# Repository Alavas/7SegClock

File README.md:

7SegClock
=========

4-Digit 7-Segment Alarm Clock

Added Lattice FGPA files.

Updated Propeller files to add MIT license.

Added new Kicad schematic.

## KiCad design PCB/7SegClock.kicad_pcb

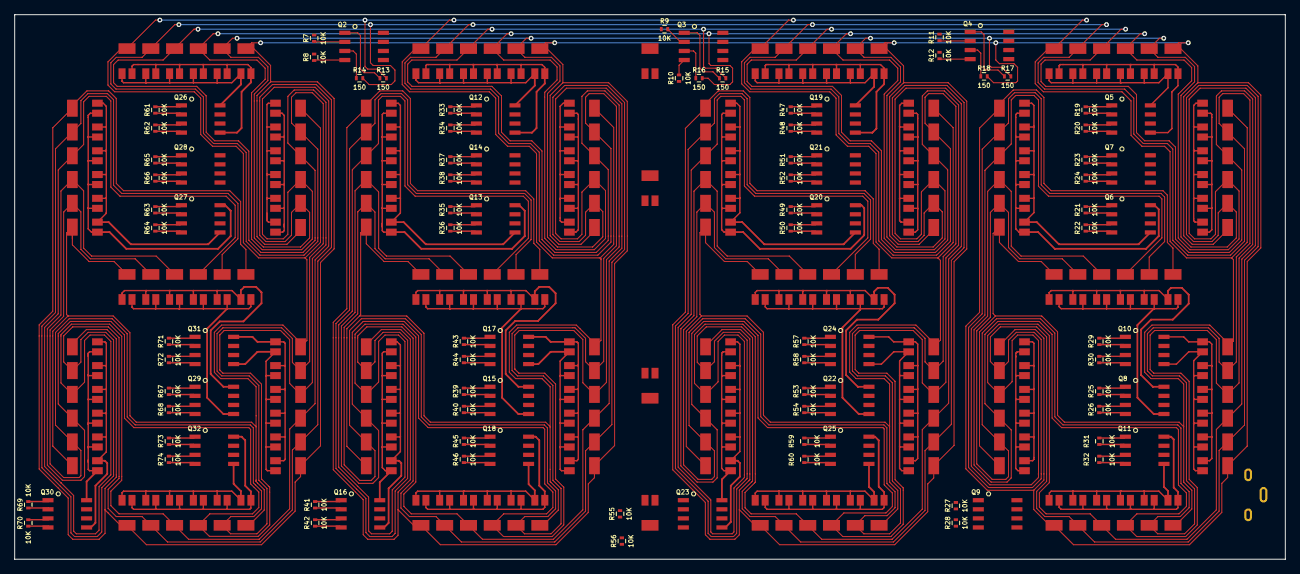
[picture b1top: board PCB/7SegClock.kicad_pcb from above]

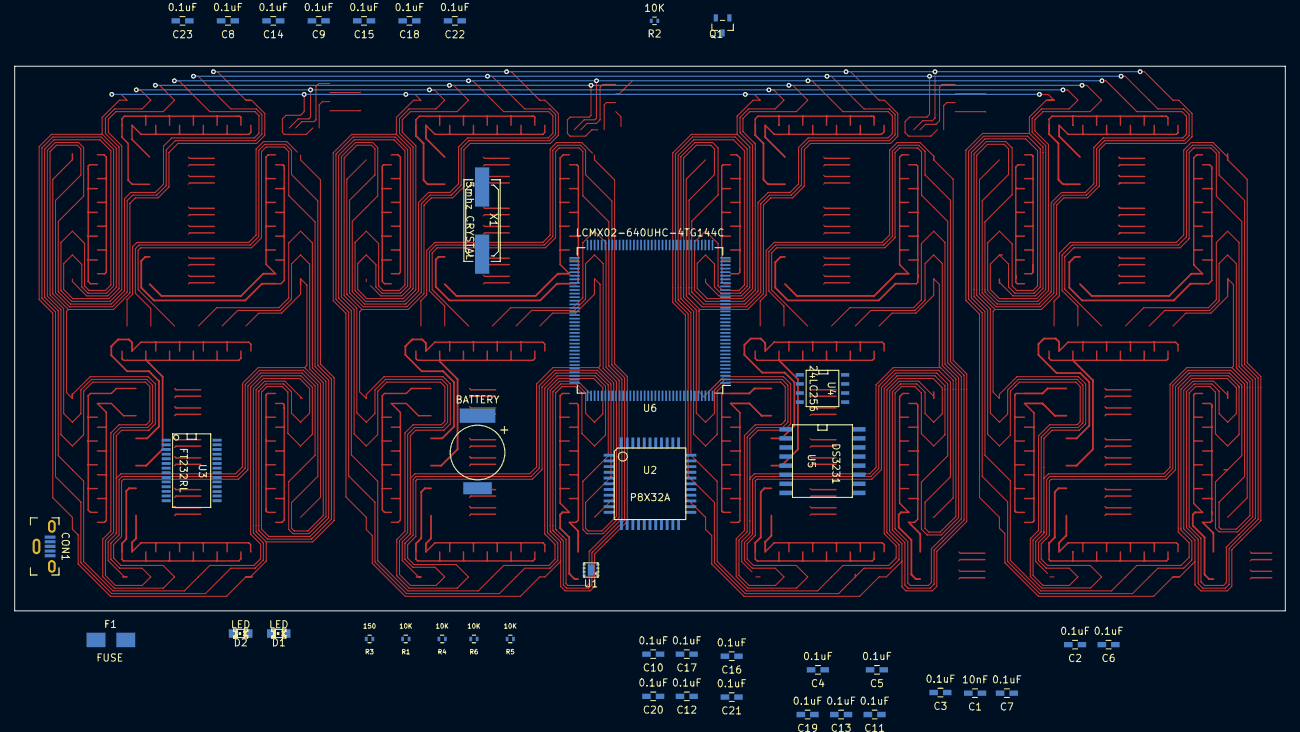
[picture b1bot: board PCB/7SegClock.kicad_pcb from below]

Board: 2 copper layers, 177.8 x 76.2 mm, 143 parts (42 on the bottom side), 158 nets.

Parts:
BT1: BATTERY; SuperCap_604-1020-1-ND
C1: 10nF; C_0603_HandSoldering
C2, C3, C4, C5, C6, C7, C8, C9, C10, C11, C12, C13, C14, C15, C16, C17, C18, C19, C20, C21, C22, C23: 0.1uF; C_0603_HandSoldering
CON1: USB_Micro_Vertical; MicroSD_Vertical
D1, D2: LED; LED-0805
D3: LED_Array; LED-ARRAY
D4: Indicators; SingleLED
F1: FUSE; Fuse_SMD1206_HandSoldering
Q1: NPN; sot23
Q2, Q3, Q4, Q5, Q6, Q7, Q8, Q9, Q10, Q11, Q12, Q13, Q14, Q15, Q16, Q17, Q18, Q19, Q20, Q21, Q22, Q23, Q24, Q25, Q26, Q27, Q28, Q29, Q30, Q31, Q32: DMN2041LSD-13; SOIC-8_3.9x4.9mm_Pitch1.27mm
R1, R2, R4, R5, R6, R7, R8, R9, R10, R11, R12, R19, R20, R21, R22, R23, R24, R25, R26, R27, R28, R29, R30, R31, R32, R33, R34, R35, R36, R37, R38, R39, R40, R41, R42, R43, R44, R45, R46, R47, R48, R49, R50, R51, R52, R53, R54, R55, R56, R57, R58, R59, R60, R61, R62, R63, R64, R65, R66, R67, R68, R69, R70, R71, R72, R73, R74: 10K; R_0402
R3, R13, R14, R15, R16, R17, R18: 150; R_0402
U1: TPS62172DSGT; WSON-8-1EP
U2: P8X32A; TQFP-44
U3: FT232RL; SSOP-28
U4: 24LC256; SOIC-8-N
U5: DS3231; SO-16-L
U6: LCMX02-640UHC-4TG144C; TQFP-144_20x20mm_Pitch0.5mm
X1: 5mhz CRYSTAL; Q_49U3HMS

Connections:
+3V3: C2.2, C3.2, C4.2, C5.2, C6.2, C7.2, C8.2, C9.2, C10.2, C11.2, C12.2, C13.2, C14.2, C15.2, C16.2, C17.2, C18.2, C19.2, C20.2, C21.2, C22.2, C23.2, R1.1, R4.1, R5.1, R6.1, U2.8, U2.18, U2.30, U2.40, U4.8, U5.2, U6.7, U6.16, U6.30, U6.36, U6.37, U6.51, U6.66, U6.72, U6.79, U6.88, U6.102, U6.108, U6.118, U6.123, U6.135, U6.144
+5V: F1.2, Q2.5, Q2.8, Q3.5, Q3.8, Q4.5, Q4.8, R3.2, U3.19, U3.20
/Lattice MACHXO2/CLK: U2.22, U6.111
/Lattice MACHXO2/CS_Clock: U2.21, U6.112
/Lattice MACHXO2/CS_Encoder: U2.19, U6.114
/Lattice MACHXO2/CS_PWM: U2.20, U6.113
/Lattice MACHXO2/DataIN: U2.24, U6.109
/Lattice MACHXO2/DataOUT: U2.23, U6.110
/Lattice MACHXO2/Digit_1/A1: D3.1, D3.19, D3.37, D3.55, D3.73, D3.91, D3.109, D3.127, D3.145, D3.163, D3.181, D3.199, D3.217, D3.235, D3.253, D3.271, D3.289, D3.307, D3.325, D3.343, D3.361, D3.379, D3.397, D3.415, D3.433, D3.451, D3.469, D3.487, R13.2
/Lattice MACHXO2/Digit_1/A2: D3.4, D3.22, D3.40, D3.58, D3.76, D3.94, D3.112, D3.130, D3.148, D3.166, D3.184, D3.202, D3.220, D3.238, D3.256, D3.274, D3.292, D3.310, D3.328, D3.346, D3.364, D3.382, D3.400, D3.418, D3.436, D3.454, D3.472, D3.490, R14.2
/Lattice MACHXO2/Digit_1/A3: D3.7, D3.25, D3.43, D3.61, D3.79, D3.97, D3.115, D3.133, D3.151, D3.169, D3.187, D3.205, D3.223, D3.241, D3.259, D3.277, D3.295, D3.313, D3.331, D3.349, D3.367, D3.385, D3.403, D3.421, D3.439, D3.457, D3.475, D3.493, R15.2
/Lattice MACHXO2/Digit_1/A4: D3.10, D3.28, D3.46, D3.64, D3.82, D3.100, D3.118, D3.136, D3.154, D3.172, D3.190, D3.208, D3.226, D3.244, D3.262, D3.280, D3.298, D3.316, D3.334, D3.352, D3.370, D3.388, D3.406, D3.424, D3.442, D3.460, D3.478, D3.496, R16.2
/Lattice MACHXO2/Digit_1/A5: D3.13, D3.31, D3.49, D3.67, D3.85, D3.103, D3.121, D3.139, D3.157, D3.175, D3.193, D3.211, D3.229, D3.247, D3.265, D3.283, D3.301, D3.319, D3.337, D3.355, D3.373, D3.391, D3.409, D3.427, D3.445, D3.463, D3.481, D3.499, R17.2
/Lattice MACHXO2/Digit_1/A6: D3.16, D3.34, D3.52, D3.70, D3.88, D3.106, D3.124, D3.142, D3.160, D3.178, D3.196, D3.214, D3.232, D3.250, D3.268, D3.286, D3.304, D3.322, D3.340, D3.358, D3.376, D3.394, D3.412, D3.430, D3.448, D3.466, D3.484, D3.502, R18.2
/Lattice MACHXO2/Digit_1/D1S1G: Q26.4, R62.1
/Lattice MACHXO2/Digit_1/D1S1R: Q26.2, R61.1
/Lattice MACHXO2/Digit_1/D1S2G: Q28.4, R66.1
/Lattice MACHXO2/Digit_1/D1S2R: Q28.2, R65.1
/Lattice MACHXO2/Digit_1/D1S3G: Q31.4, R72.1
/Lattice MACHXO2/Digit_1/D1S3R: Q31.2, R71.1
/Lattice MACHXO2/Digit_1/D1S4G: Q32.4, R74.1
/Lattice MACHXO2/Digit_1/D1S4R: Q32.2, R73.1
/Lattice MACHXO2/Digit_1/D1S5G: Q30.4, R70.1
/Lattice MACHXO2/Digit_1/D1S5R: Q30.2, R69.1
/Lattice MACHXO2/Digit_1/D1S6G: Q27.4, R64.1
/Lattice MACHXO2/Digit_1/D1S6R: Q27.2, R63.1
/Lattice MACHXO2/Digit_1/D1S7G: Q29.4, R68.1
/Lattice MACHXO2/Digit_1/D1S7R: Q29.2, R67.1
/Lattice MACHXO2/Digit_2/D2S1G: Q12.4, R34.1
/Lattice MACHXO2/Digit_2/D2S1R: Q12.2, R33.1
/Lattice MACHXO2/Digit_2/D2S2G: Q14.4, R38.1
/Lattice MACHXO2/Digit_2/D2S2R: Q14.2, R37.1
/Lattice MACHXO2/Digit_2/D2S3G: Q17.4, R44.1
/Lattice MACHXO2/Digit_2/D2S3R: Q17.2, R43.1
/Lattice MACHXO2/Digit_2/D2S4G: Q18.4, R46.1
/Lattice MACHXO2/Digit_2/D2S4R: Q18.2, R45.1
/Lattice MACHXO2/Digit_2/D2S5G: Q16.4, R42.1
/Lattice MACHXO2/Digit_2/D2S5R: Q16.2, R41.1
/Lattice MACHXO2/Digit_2/D2S6G: Q13.4, R36.1
/Lattice MACHXO2/Digit_2/D2S6R: Q13.2, R35.1
/Lattice MACHXO2/Digit_2/D2S7G: Q15.4, R40.1
/Lattice MACHXO2/Digit_2/D2S7R: Q15.2, R39.1
/Lattice MACHXO2/Digit_3/D3S1G: Q19.4, R48.1
/Lattice MACHXO2/Digit_3/D3S1R: Q19.2, R47.1
/Lattice MACHXO2/Digit_3/D3S2G: Q21.4, R52.1
/Lattice MACHXO2/Digit_3/D3S2R: Q21.2, R51.1
/Lattice MACHXO2/Digit_3/D3S3G: Q24.4, R58.1
/Lattice MACHXO2/Digit_3/D3S3R: Q24.2, R57.1
/Lattice MACHXO2/Digit_3/D3S4G: Q25.4, R60.1
/Lattice MACHXO2/Digit_3/D3S4R: Q25.2, R59.1
/Lattice MACHXO2/Digit_3/D3S5G: Q23.4, R56.1
/Lattice MACHXO2/Digit_3/D3S5R: Q23.2, R55.1
/Lattice MACHXO2/Digit_3/D3S6G: Q20.4, R50.1
/Lattice MACHXO2/Digit_3/D3S6R: Q20.2, R49.1
/Lattice MACHXO2/Digit_3/D3S7G: Q22.4, R54.1
/Lattice MACHXO2/Digit_3/D3S7R: Q22.2, R53.1
/Lattice MACHXO2/Digit_4/D4S1G: Q5.4, R20.1
/Lattice MACHXO2/Digit_4/D4S1R: Q5.2, R19.1
/Lattice MACHXO2/Digit_4/D4S2G: Q7.4, R24.1
/Lattice MACHXO2/Digit_4/D4S2R: Q7.2, R23.1
/Lattice MACHXO2/Digit_4/D4S3G: Q10.4, R30.1
/Lattice MACHXO2/Digit_4/D4S3R: Q10.2, R29.1
/Lattice MACHXO2/Digit_4/D4S4G: Q11.4, R32.1
/Lattice MACHXO2/Digit_4/D4S4R: Q11.2, R31.1
/Lattice MACHXO2/Digit_4/D4S5G: Q9.4, R28.1
/Lattice MACHXO2/Digit_4/D4S5R: Q9.2, R27.1
/Lattice MACHXO2/Digit_4/D4S6G: Q6.4, R22.1
/Lattice MACHXO2/Digit_4/D4S6R: Q6.2, R21.1
/Lattice MACHXO2/Digit_4/D4S7G: Q8.4, R26.1
/Lattice MACHXO2/Digit_4/D4S7R: Q8.2, R25.1
CLK_INT: R4.2, U5.3
DTR: Q1.3, R1.2, U2.7
GND: BT1.2, C2.1, C3.1, C8.1, C9.1, C10.1, C11.1, C12.1, C13.1, C14.1, C15.1, C16.1, C17.1, C18.1, C19.1, C20.1, C21.1, C22.1, C23.1, CON1.5, CON1.6, CON1.7, CON1.8, Q1.1, Q5.1, Q5.3, Q6.1, Q6.3, Q7.1, Q7.3, Q8.1, Q8.3, Q9.1, Q9.3, Q10.1, Q10.3, Q11.1, Q11.3, Q12.1, Q12.3, Q13.1, Q13.3, Q14.1, Q14.3, Q15.1, Q15.3, Q16.1, Q16.3, Q17.1, Q17.3, Q18.1, Q18.3, Q19.1, Q19.3, Q20.1, Q20.3, Q21.1, Q21.3, Q22.1, Q22.3, Q23.1, Q23.3, Q24.1, Q24.3, Q25.1, Q25.3, Q26.1, Q26.3, Q27.1, Q27.3, Q28.1, Q28.3, Q29.1, Q29.3, Q30.1, Q30.3, Q31.1, Q31.3, Q32.1, Q32.3, R2.2, R7.2, R8.2, R9.2, R10.2, R11.2, R12.2, R19.2, R20.2, R21.2, R22.2, R23.2, R24.2, R25.2, R26.2, R27.2, R28.2, R29.2, R30.2, R31.2, R32.2, R33.2, R34.2, R35.2, R36.2, R37.2, R38.2, R39.2, R40.2, R41.2, R42.2, R43.2, R44.2, R45.2, R46.2, R47.2, R48.2, R49.2, R50.2, R51.2, R52.2, R53.2, R54.2, R55.2, R56.2, R57.2, R58.2, R59.2, R60.2, R61.2, R62.2, R63.2, R64.2, R65.2, R66.2, R67.2, R68.2, R69.2, R70.2, R71.2, R72.2, R73.2, R74.2, U2.5, U2.6, U2.17, U2.27, U2.39, U3.7, U3.18, U3.21, U3.25, U3.26, U4.1, U4.2, U4.3, U4.4, U4.7, U5.5, U5.6, U5.7, U5.8, U5.9, U5.10, U5.11, U5.12, U5.13, U6.8, U6.18, U6.29, U6.46, U6.53, U6.64, U6.80, U6.90, U6.101, U6.116, U6.124, U6.134
unnamed: BT1.1, U5.14
unnamed: C1.1, Q1.2, R2.1
unnamed: C1.2, U3.2
unnamed: C4.1, C5.1, C6.1, C7.1
unnamed: CON1.2, U3.15
unnamed: CON1.3, U3.16
unnamed: D1.1, D2.1, R3.1
unnamed: D1.2, U3.22
unnamed: D2.2, U3.23
unnamed: D3.2, D3.5, D3.8, D3.11, D3.14, D3.17, Q26.8
unnamed: D3.3, D3.6, D3.9, D3.12, D3.15, D3.18, Q26.5
unnamed: D3.20, D3.23, D3.26, D3.29, D3.32, D3.35, Q28.8
unnamed: D3.21, D3.24, D3.27, D3.30, D3.33, D3.36, Q28.5
unnamed: D3.38, D3.41, D3.44, D3.47, D3.50, D3.53, Q31.8
unnamed: D3.39, D3.42, D3.45, D3.48, D3.51, D3.54, Q31.5
unnamed: D3.56, D3.59, D3.62, D3.65, D3.68, D3.71, Q32.8
unnamed: D3.57, D3.60, D3.63, D3.66, D3.69, D3.72, Q32.5
unnamed: D3.74, D3.77, D3.80, D3.83, D3.86, D3.89, Q30.8
unnamed: D3.75, D3.78, D3.81, D3.84, D3.87, D3.90, Q30.5
unnamed: D3.92, D3.95, D3.98, D3.101, D3.104, D3.107, Q27.8
unnamed: D3.93, D3.96, D3.99, D3.102, D3.105, D3.108, Q27.5
unnamed: D3.110, D3.113, D3.116, D3.119, D3.122, D3.125, Q29.8
unnamed: D3.111, D3.114, D3.117, D3.120, D3.123, D3.126, Q29.5
unnamed: D3.128, D3.131, D3.134, D3.137, D3.140, D3.143, Q12.8
unnamed: D3.129, D3.132, D3.135, D3.138, D3.141, D3.144, Q12.5
unnamed: D3.146, D3.149, D3.152, D3.155, D3.158, D3.161, Q14.8
unnamed: D3.147, D3.150, D3.153, D3.156, D3.159, D3.162, Q14.5
unnamed: D3.164, D3.167, D3.170, D3.173, D3.176, D3.179, Q17.8
unnamed: D3.165, D3.168, D3.171, D3.174, D3.177, D3.180, Q17.5
unnamed: D3.182, D3.185, D3.188, D3.191, D3.194, D3.197, Q18.8
unnamed: D3.183, D3.186, D3.189, D3.192, D3.195, D3.198, Q18.5
unnamed: D3.200, D3.203, D3.206, D3.209, D3.212, D3.215, Q16.8
unnamed: D3.201, D3.204, D3.207, D3.210, D3.213, D3.216, Q16.5
unnamed: D3.218, D3.221, D3.224, D3.227, D3.230, D3.233, Q13.8
unnamed: D3.219, D3.222, D3.225, D3.228, D3.231, D3.234, Q13.5
unnamed: D3.236, D3.239, D3.242, D3.245, D3.248, D3.251, Q15.8
unnamed: D3.237, D3.240, D3.243, D3.246, D3.249, D3.252, Q15.5
unnamed: D3.254, D3.257, D3.260, D3.263, D3.266, D3.269, Q19.8
unnamed: D3.255, D3.258, D3.261, D3.264, D3.267, D3.270, Q19.5
unnamed: D3.272, D3.275, D3.278, D3.281, D3.284, D3.287, Q21.8
unnamed: D3.273, D3.276, D3.279, D3.282, D3.285, D3.288, Q21.5
unnamed: D3.290, D3.293, D3.296, D3.299, D3.302, D3.305, Q24.8
unnamed: D3.291, D3.294, D3.297, D3.300, D3.303, D3.306, Q24.5
unnamed: D3.308, D3.311, D3.314, D3.317, D3.320, D3.323, Q25.8
unnamed: D3.309, D3.312, D3.315, D3.318, D3.321, D3.324, Q25.5
unnamed: D3.326, D3.329, D3.332, D3.335, D3.338, D3.341, Q23.8
unnamed: D3.327, D3.330, D3.333, D3.336, D3.339, D3.342, Q23.5
unnamed: D3.344, D3.347, D3.350, D3.353, D3.356, D3.359, Q20.8
unnamed: D3.345, D3.348, D3.351, D3.354, D3.357, D3.360, Q20.5
unnamed: D3.362, D3.365, D3.368, D3.371, D3.374, D3.377, Q22.8
unnamed: D3.363, D3.366, D3.369, D3.372, D3.375, D3.378, Q22.5
unnamed: D3.380, D3.383, D3.386, D3.389, D3.392, D3.395, Q5.8
unnamed: D3.381, D3.384, D3.387, D3.390, D3.393, D3.396, Q5.5
unnamed: D3.398, D3.401, D3.404, D3.407, D3.410, D3.413, Q7.8
unnamed: D3.399, D3.402, D3.405, D3.408, D3.411, D3.414, Q7.5
unnamed: D3.416, D3.419, D3.422, D3.425, D3.428, D3.431, Q10.8
unnamed: D3.417, D3.420, D3.423, D3.426, D3.429, D3.432, Q10.5
unnamed: D3.434, D3.437, D3.440, D3.443, D3.446, D3.449, Q11.8
unnamed: D3.435, D3.438, D3.441, D3.444, D3.447, D3.450, Q11.5
unnamed: D3.452, D3.455, D3.458, D3.461, D3.464, D3.467, Q9.8
unnamed: D3.453, D3.456, D3.459, D3.462, D3.465, D3.468, Q9.5
unnamed: D3.470, D3.473, D3.476, D3.479, D3.482, D3.485, Q6.8
unnamed: D3.471, D3.474, D3.477, D3.480, D3.483, D3.486, Q6.5
unnamed: D3.488, D3.491, D3.494, D3.497, D3.500, D3.503, Q8.8
unnamed: D3.489, D3.492, D3.495, D3.498, D3.501, D3.504, Q8.5
unnamed: Q2.1, R13.1
unnamed: Q2.2, R7.1
unnamed: Q2.3, R14.1
unnamed: Q2.4, R8.1
unnamed: Q3.1, R15.1
unnamed: Q3.2, R9.1
unnamed: Q3.3, R16.1
unnamed: Q3.4, R10.1
unnamed: Q4.1, R17.1
unnamed: Q4.2, R11.1
unnamed: Q4.3, R18.1
unnamed: Q4.4, R12.1
unnamed: U2.28, X1.1
unnamed: U2.29, X1.2
unnamed: U2.37, U3.5
unnamed: U2.38, U3.1
unnamed: U3.4, U3.17
SCL: R5.2, U2.35, U4.6, U5.16, U6.126
SDA: R6.2, U2.36, U4.5, U5.15, U6.125
VIN: CON1.1, F1.1

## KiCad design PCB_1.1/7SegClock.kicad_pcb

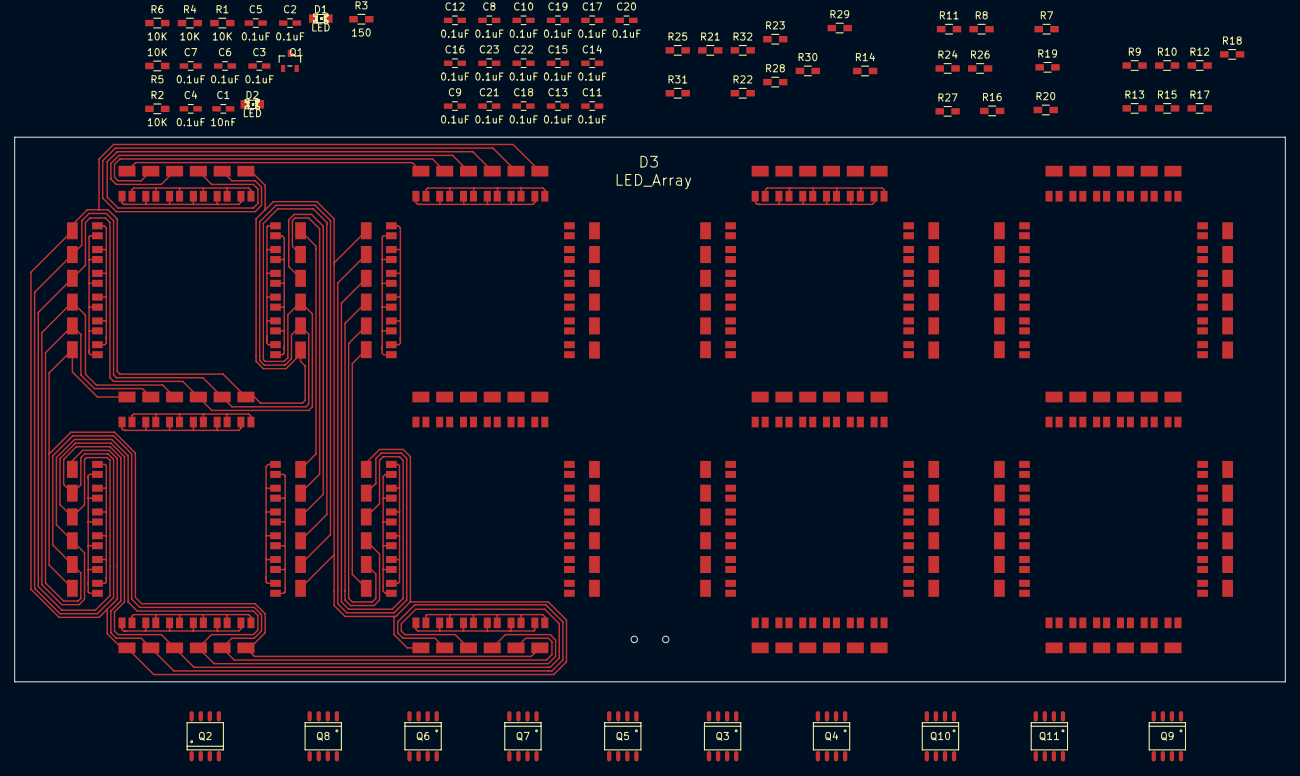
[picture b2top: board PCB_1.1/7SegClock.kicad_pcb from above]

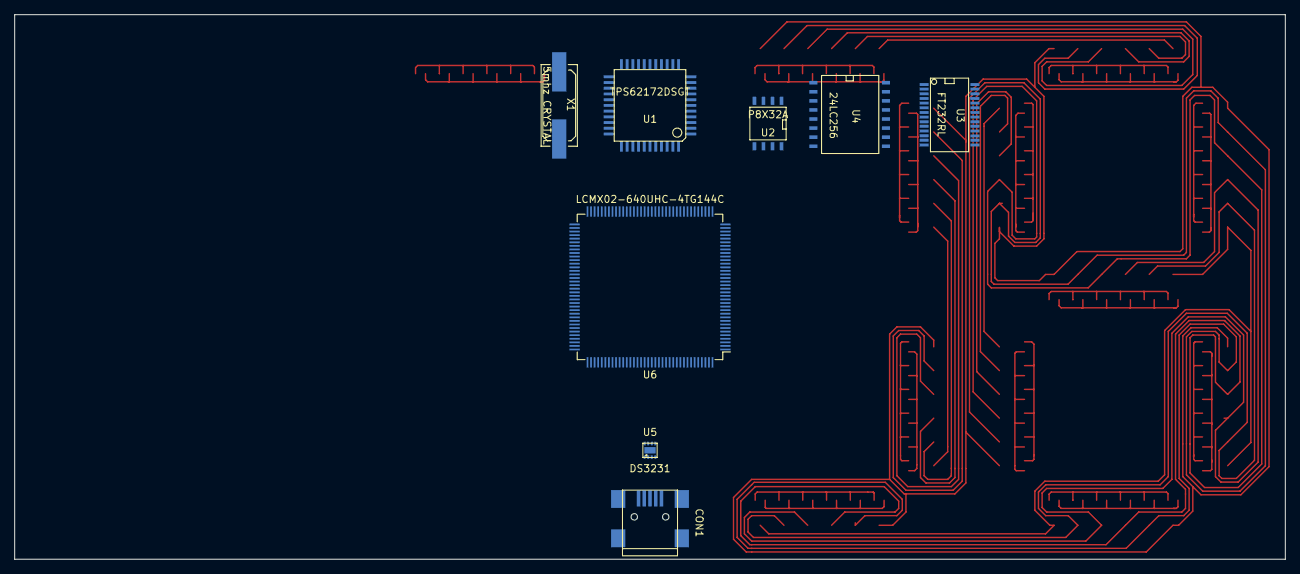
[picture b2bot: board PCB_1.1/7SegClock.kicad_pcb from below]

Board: 2 copper layers, 177.8 x 76.2 mm, 77 parts (8 on the bottom side), 48 nets.

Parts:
C1: 10nF; C_0603_HandSoldering
C2, C3, C4, C5, C6, C7, C8, C9, C10, C11, C12, C13, C14, C15, C16, C17, C18, C19, C20, C21, C22, C23: 0.1uF; C_0603_HandSoldering
CON1: USB-MINI-B; USB_Mini-B
D1, D2: LED; LED-0805
D3: LED_Array; LED-ARRAY
Q1: NPN; sot23
Q2, Q3, Q4, Q5, Q6, Q7, Q8, Q9, Q10, Q11: DMN2041LSD-13; SO-8
R1, R2, R4, R5, R6, R7, R8, R9, R10, R11, R12, R15, R16, R17, R18, R19, R20, R23, R24, R25, R26, R27, R28, R31, R32: 10K; R_0603_HandSoldering
R3, R13, R14, R21, R22, R29, R30: 150; R_0603_HandSoldering
U1: TPS62172DSGT; TQFP-44
U2: P8X32A; SOIC-8-N
U3: FT232RL; SSOP-28
U4: 24LC256; SO-16-W
U5: DS3231; WSON-8-1EP
U6: LCMX02-640UHC-4TG144C; TQFP-144_20x20mm_Pitch0.5mm
X1: 5mhz CRYSTAL; Q_49U3HMS

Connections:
+3V3: C2.2, C3.2, C4.2, C5.2, C6.2, C7.2, C8.2, C9.2, C10.2, C11.2, C12.2, C13.2, C14.2, C15.2, C16.2, C17.2, C18.2, C19.2, C20.2, C21.2, C22.2, C23.2, R1.1, R4.1, R5.1, R6.1, U2.8, U4.8, U5.2, U6.7, U6.16, U6.30, U6.36, U6.37, U6.51, U6.66, U6.72, U6.79, U6.88, U6.102, U6.108, U6.118, U6.123, U6.135, U6.144
+5V: Q4.5, Q4.8, Q7.5, Q7.8, Q10.5, Q10.8, R3.2, U3.19, U3.20
/Lattice MACHXO2/Digit Drivers/A1: Q4.2, R11.1
/Lattice MACHXO2/Digit Drivers/A2: Q4.4, R12.1
/Lattice MACHXO2/Digit Drivers/A3: Q7.2, R19.1
/Lattice MACHXO2/Digit Drivers/A4: Q7.4, R20.1
/Lattice MACHXO2/Digit Drivers/A5: Q10.2, R27.1
/Lattice MACHXO2/Digit Drivers/A6: Q10.4, R28.1
/Lattice MACHXO2/Digit Drivers/Digit 1/D1A1: D3.1, D3.19, D3.37, D3.55, D3.73, D3.91, D3.109, D3.127, D3.145, D3.163, D3.181, D3.199, D3.217, D3.235, D3.253, D3.271, D3.289, D3.307, D3.325, D3.343, D3.361, D3.379, D3.397, D3.415, D3.433, D3.451, D3.469, D3.487, R13.2
/Lattice MACHXO2/Digit Drivers/Digit 1/D1A2: D3.4, D3.22, D3.40, D3.58, D3.76, D3.94, D3.112, D3.130, D3.148, D3.166, D3.184, D3.202, D3.220, D3.238, D3.256, D3.274, D3.292, D3.310, D3.328, D3.346, D3.364, D3.382, D3.400, D3.418, D3.436, D3.454, D3.472, D3.490, R14.2
/Lattice MACHXO2/Digit Drivers/Digit 1/D1A3: D3.7, D3.25, D3.43, D3.61, D3.79, D3.97, D3.115, D3.133, D3.151, D3.169, D3.187, D3.205, D3.223, D3.241, D3.259, D3.277, D3.295, D3.313, D3.331, D3.349, D3.367, D3.385, D3.403, D3.421, D3.439, D3.457, D3.475, D3.493, R21.2
/Lattice MACHXO2/Digit Drivers/Digit 1/D1A4: D3.10, D3.28, D3.46, D3.64, D3.82, D3.100, D3.118, D3.136, D3.154, D3.172, D3.190, D3.208, D3.226, D3.244, D3.262, D3.280, D3.298, D3.316, D3.334, D3.352, D3.370, D3.388, D3.406, D3.424, D3.442, D3.460, D3.478, D3.496, R22.2
/Lattice MACHXO2/Digit Drivers/Digit 1/D1A5: D3.13, D3.31, D3.49, D3.67, D3.85, D3.103, D3.121, D3.139, D3.157, D3.175, D3.193, D3.211, D3.229, D3.247, D3.265, D3.283, D3.301, D3.319, D3.337, D3.355, D3.373, D3.391, D3.409, D3.427, D3.445, D3.463, D3.481, D3.499, R29.2
/Lattice MACHXO2/Digit Drivers/Digit 1/D1A6: D3.16, D3.34, D3.52, D3.70, D3.88, D3.106, D3.124, D3.142, D3.160, D3.178, D3.196, D3.214, D3.232, D3.250, D3.268, D3.286, D3.304, D3.322, D3.340, D3.358, D3.376, D3.394, D3.412, D3.430, D3.448, D3.466, D3.484, D3.502, R30.2
/Lattice MACHXO2/Digit Drivers/S1G: D3.3, D3.6, D3.9, D3.12, D3.15, D3.18, D3.129, D3.132, D3.135, D3.138, D3.141, D3.144, D3.255, D3.258, D3.261, D3.264, D3.267, D3.270, D3.381, D3.384, D3.387, D3.390, D3.393, D3.396, Q2.2, R7.1
/Lattice MACHXO2/Digit Drivers/S1R: D3.2, D3.5, D3.8, D3.11, D3.14, D3.17, D3.128, D3.131, D3.134, D3.137, D3.140, D3.143, D3.254, D3.257, D3.260, D3.263, D3.266, D3.269, D3.380, D3.383, D3.386, D3.389, D3.392, D3.395, Q2.4, R8.1
/Lattice MACHXO2/Digit Drivers/S2G: D3.21, D3.24, D3.27, D3.30, D3.33, D3.36, D3.147, D3.150, D3.153, D3.156, D3.159, D3.162, D3.273, D3.276, D3.279, D3.282, D3.285, D3.288, D3.399, D3.402, D3.405, D3.408, D3.411, D3.414, Q5.2, R15.1
/Lattice MACHXO2/Digit Drivers/S2R: D3.20, D3.23, D3.26, D3.29, D3.32, D3.35, D3.146, D3.149, D3.152, D3.155, D3.158, D3.161, D3.272, D3.275, D3.278, D3.281, D3.284, D3.287, D3.398, D3.401, D3.404, D3.407, D3.410, D3.413, Q5.4, R16.1
/Lattice MACHXO2/Digit Drivers/S3G: D3.39, D3.42, D3.45, D3.48, D3.51, D3.54, D3.165, D3.168, D3.171, D3.174, D3.177, D3.180, D3.291, D3.294, D3.297, D3.300, D3.303, D3.306, D3.417, D3.420, D3.423, D3.426, D3.429, D3.432, Q8.2, R23.1
/Lattice MACHXO2/Digit Drivers/S3R: D3.38, D3.41, D3.44, D3.47, D3.50, D3.53, D3.164, D3.167, D3.170, D3.173, D3.176, D3.179, D3.290, D3.293, D3.296, D3.299, D3.302, D3.305, D3.416, D3.419, D3.422, D3.425, D3.428, D3.431, Q8.4, R24.1
/Lattice MACHXO2/Digit Drivers/S4G: D3.57, D3.60, D3.63, D3.66, D3.69, D3.72, D3.183, D3.186, D3.189, D3.192, D3.195, D3.198, D3.309, D3.312, D3.315, D3.318, D3.321, D3.324, D3.435, D3.438, D3.441, D3.444, D3.447, D3.450, Q11.2, R31.1
/Lattice MACHXO2/Digit Drivers/S4R: D3.56, D3.59, D3.62, D3.65, D3.68, D3.71, D3.182, D3.185, D3.188, D3.191, D3.194, D3.197, D3.308, D3.311, D3.314, D3.317, D3.320, D3.323, D3.434, D3.437, D3.440, D3.443, D3.446, D3.449, Q11.4, R32.1
/Lattice MACHXO2/Digit Drivers/S5G: D3.75, D3.78, D3.81, D3.84, D3.87, D3.90, D3.201, D3.204, D3.207, D3.210, D3.213, D3.216, D3.327, D3.330, D3.333, D3.336, D3.339, D3.342, D3.453, D3.456, D3.459, D3.462, D3.465, D3.468, Q3.2, R9.1
/Lattice MACHXO2/Digit Drivers/S5R: D3.74, D3.77, D3.80, D3.83, D3.86, D3.89, D3.200, D3.203, D3.206, D3.209, D3.212, D3.215, D3.326, D3.329, D3.332, D3.335, D3.338, D3.341, D3.452, D3.455, D3.458, D3.461, D3.464, D3.467, Q3.4, R10.1
/Lattice MACHXO2/Digit Drivers/S6G: D3.93, D3.96, D3.99, D3.102, D3.105, D3.108, D3.219, D3.222, D3.225, D3.228, D3.231, D3.234, D3.345, D3.348, D3.351, D3.354, D3.357, D3.360, D3.471, D3.474, D3.477, D3.480, D3.483, D3.486, Q6.2, R17.1
/Lattice MACHXO2/Digit Drivers/S6R: D3.92, D3.95, D3.98, D3.101, D3.104, D3.107, D3.218, D3.221, D3.224, D3.227, D3.230, D3.233, D3.344, D3.347, D3.350, D3.353, D3.356, D3.359, D3.470, D3.473, D3.476, D3.479, D3.482, D3.485, Q6.4, R18.1
/Lattice MACHXO2/Digit Drivers/S7G: D3.111, D3.114, D3.117, D3.120, D3.123, D3.126, D3.237, D3.240, D3.243, D3.246, D3.249, D3.252, D3.363, D3.366, D3.369, D3.372, D3.375, D3.378, D3.489, D3.492, D3.495, D3.498, D3.501, D3.504, Q9.2, R25.1
/Lattice MACHXO2/Digit Drivers/S7R: D3.110, D3.113, D3.116, D3.119, D3.122, D3.125, D3.236, D3.239, D3.242, D3.245, D3.248, D3.251, D3.362, D3.365, D3.368, D3.371, D3.374, D3.377, D3.488, D3.491, D3.494, D3.497, D3.500, D3.503, Q9.4, R26.1
CLK_INT: R4.2, U5.3
DTR: Q1.3, R1.2, U2.7
GND: C2.1, C3.1, C8.1, C9.1, C10.1, C11.1, C12.1, C13.1, C14.1, C15.1, C16.1, C17.1, C18.1, C19.1, C20.1, C21.1, C22.1, C23.1, CON1.5, CON1.6, CON1.7, CON1.8, CON1.9, Q1.1, Q2.1, Q2.3, Q3.1, Q3.3, Q5.1, Q5.3, Q6.1, Q6.3, Q8.1, Q8.3, Q9.1, Q9.3, Q11.1, Q11.3, R2.2, R7.2, R8.2, R9.2, R10.2, R11.2, R12.2, R15.2, R16.2, R17.2, R18.2, R19.2, R20.2, R23.2, R24.2, R25.2, R26.2, R27.2, R28.2, R31.2, R32.2, U2.5, U2.6, U3.7, U3.18, U3.21, U3.25, U3.26, U4.1, U4.2, U4.3, U4.4, U4.7, U5.5, U5.6, U5.7, U5.8, U5.9, U6.8, U6.18, U6.29, U6.46, U6.53, U6.64, U6.80, U6.90, U6.101, U6.116, U6.124, U6.134
unnamed: C1.1, Q1.2, R2.1
unnamed: C1.2, U3.2
unnamed: C4.1, C5.1, C6.1, C7.1
unnamed: CON1.2, U3.15
unnamed: CON1.3, U3.16
unnamed: D1.1, D2.1, R3.1
unnamed: D1.2, U3.22
unnamed: D2.2, U3.23
unnamed: Q4.1, R13.1
unnamed: Q4.3, R14.1
unnamed: Q7.1, R21.1
unnamed: Q7.3, R22.1
unnamed: Q10.1, R29.1
unnamed: Q10.3, R30.1
unnamed: U3.4, U3.17
SCL: R5.2, U4.6, U6.126
SDA: R6.2, U4.5, U6.125

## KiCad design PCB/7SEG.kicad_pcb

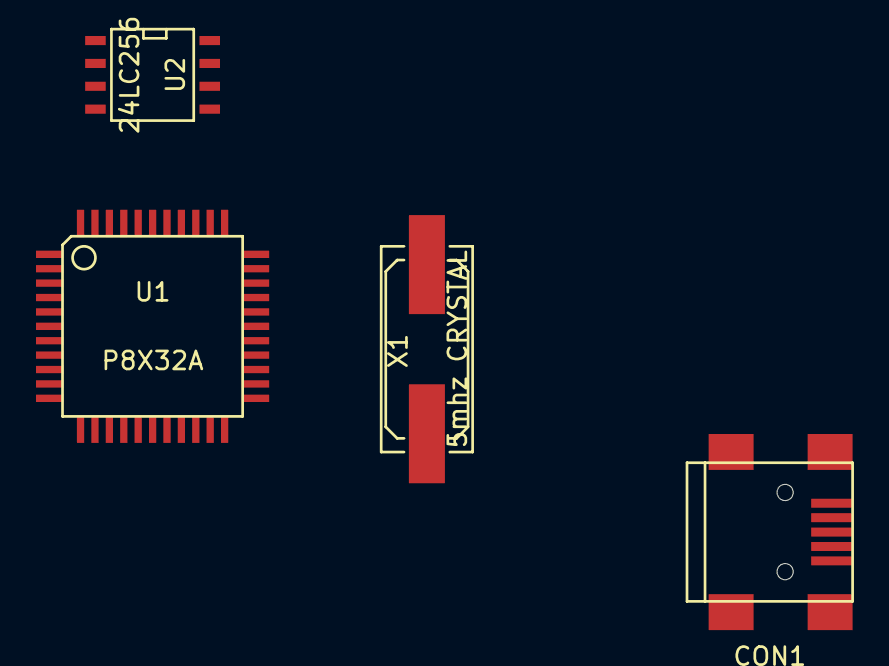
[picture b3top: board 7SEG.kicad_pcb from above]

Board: 2 copper layers, 4 parts (0 on the bottom side), 5 nets, no tracks yet.

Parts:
CON1: USB-MINI-B; USB_Mini-B
U1: P8X32A; TQFP-44
U2: 24LC256; SOIC-8-N
X1: 5mhz CRYSTAL; Q_49U3HMS

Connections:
GND: U1.5, U1.17, U1.27, U1.39, U2.1, U2.2, U2.3, U2.4, U2.7
unnamed: U1.28, X1.1
unnamed: U1.29, X1.2
SCL: U1.35, U2.6
SDA: U1.36, U2.5

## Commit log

2014-12-26 test
2014-12-26 added Propeller files
2014-12-27 modified Readme
2014-12-27 Modded readme
2014-12-27 Added PCB project.
2014-12-27 Reorganized files.
2014-12-27 Remove files.
2014-12-27 Deleted duplicate items.
2014-12-28 Create new library.
2014-12-28 Schematic work.
2014-12-28 Updated schematic.
2014-12-28 Add file.
2014-12-28 Update readme.
2014-12-28 Removed DS_store
2014-12-28 Worked on schematic.
2014-12-28 Updated files.
2014-12-28 Deleted file.
2014-12-29 Schematic progress.
2014-12-30 Added Lattice FPGA files.
2014-12-30 Generated svf file.
2014-12-30 Readme
2014-12-31 Worked on FPGA.
2015-01-01 Worked on FPGA
2015-01-02 Added license to Propeller Programs
2015-01-02 Edited Readme
2015-01-03 Added photos folder.
2015-01-03 Remove file.
2015-01-03 FPGA work.
2015-01-04 FPGA issues.
2015-01-04 FPGA
2015-01-04 Removed redundancy.
2015-01-04 Deleted files.
2015-01-06 Worked on FPGA functionality. Switched to smaller device.
2015-01-13 FPGA edit.
2015-01-13 Worked on PCB, added FPGA.
2015-01-13 Worked on PCB.
2015-01-14 Worked on LED array.
2015-01-15 Added new footprint.
2015-01-15 Updated libraries.
2015-01-16 Worked on LED array footprint.
2015-01-18 Finished LED array footprint.
2015-01-22 PCB work.
2015-01-26 Worked on PCB
2015-01-28 Edited file names.
2015-02-25 Updated mosfets.
2015-03-15 Fixing errors.
2015-03-15 Errors fixed.
2015-03-15 FPGA test code.
2015-03-16 Modified FPGA code.
2015-03-21 FPGA work, added PWM.
2015-03-25 Updated FPGA code.
2015-07-08 Modified schematic.
2015-07-08 Added additional mosfets.
2015-07-10 Edit PCB.
2015-07-18 Added new files for revised PCB design.
2016-12-24 Removed old directory.
2017-02-25 Updated verilog file.
2017-02-25 Remove DS_Store
